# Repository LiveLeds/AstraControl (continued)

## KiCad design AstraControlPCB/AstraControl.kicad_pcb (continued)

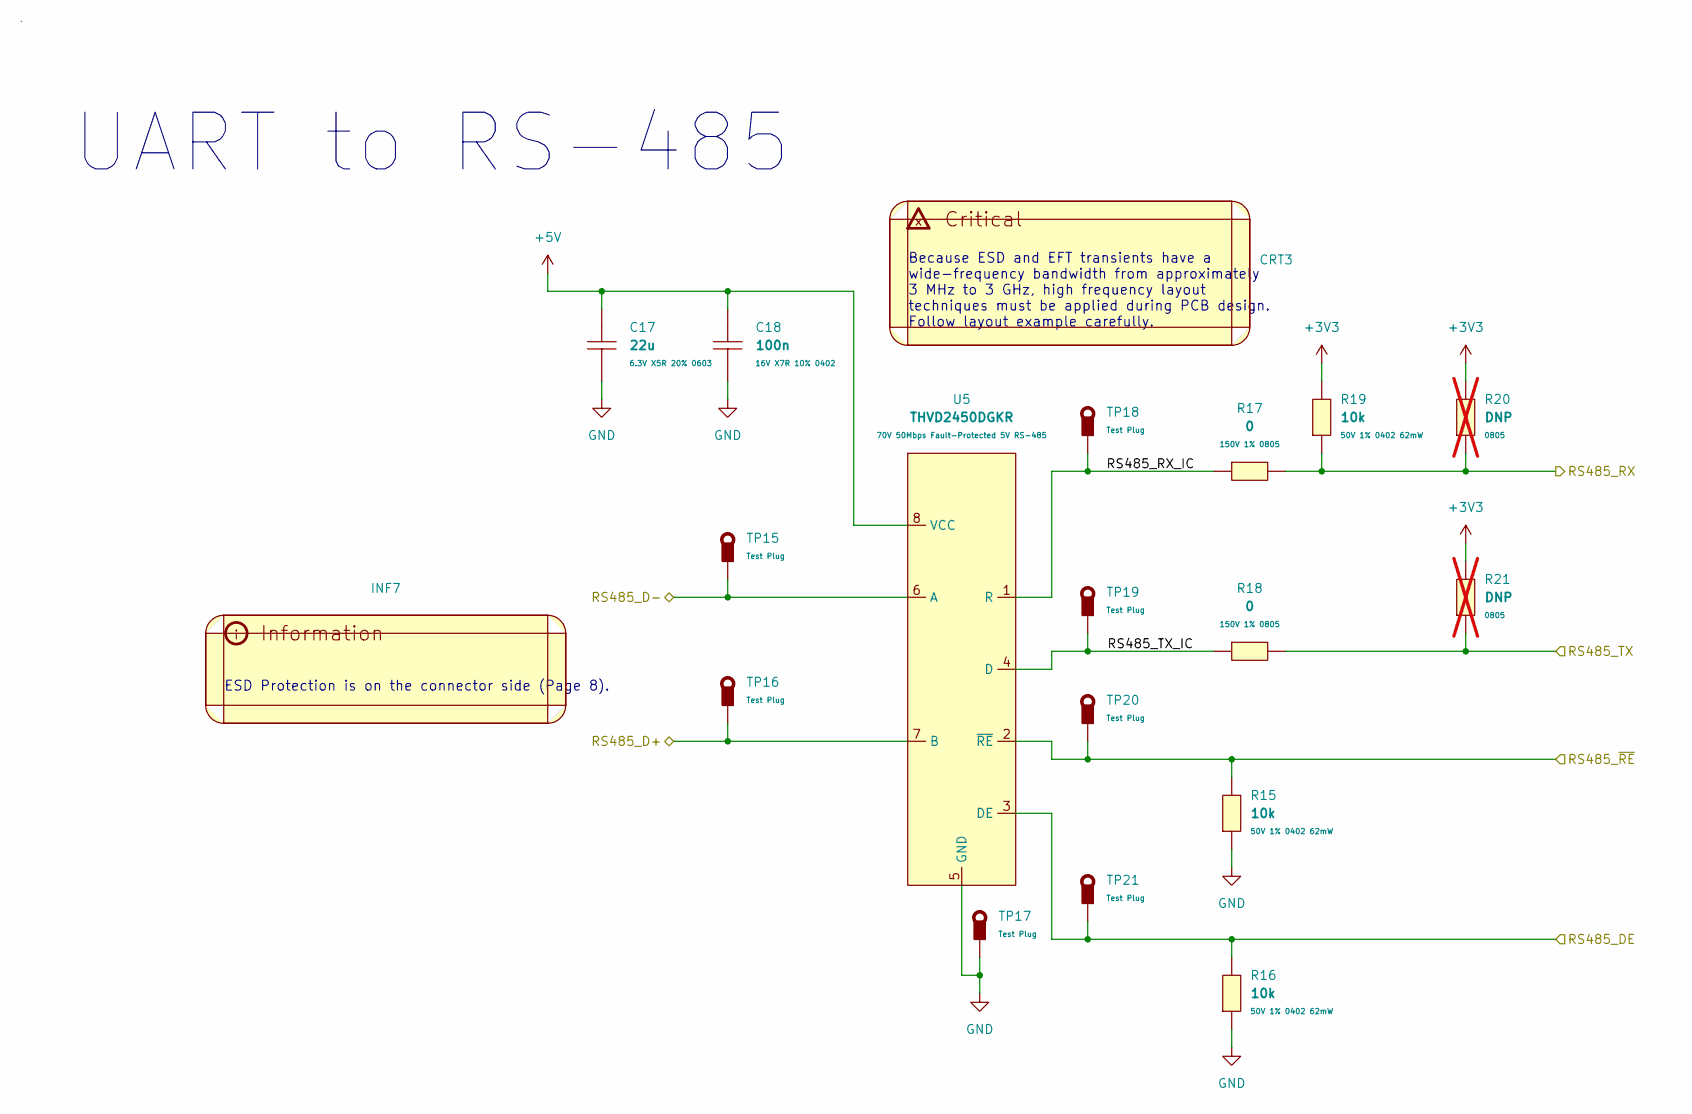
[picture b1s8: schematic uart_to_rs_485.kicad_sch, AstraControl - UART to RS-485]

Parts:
C17: 22u; C_0603_1608Metric; MPN CL10A226MQ8NRNC; LCSC Part C59461
C18: 100n; C_0402_1005Metric; MPN CL05B104KO5NNNC; LCSC Part C1525
CRT3: (no value)
INF7: (no value)
R15, R16, R19: 10k; R_0402_1005Metric; MPN 0402WGF1002TCE; LCSC Part C25744
R17, R18: 0; R_0805_2012Metric_Pad1.20x1.40mm_HandSolder; MPN 0805W8F0000T5E; LCSC Part C17477
R20, R21: DNP; R_DNP_0805_2012Metric_Pad1.20x1.40mm_HandSolder; not fitted
TP15, TP16, TP17, TP18, TP19, TP20, TP21: TestPoint_Thimble; TestPoint_Loop_D3.50mm_Drill0.9mm_Beaded; MPN RH-5000; LCSC Part C5277086
U5: THVD2450DGKR; THVD2450DGKR_RS485_Transciever_VSSOP8; MPN THVD2450DGKR; LCSC Part C3246171

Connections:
+3V3: R19.2, R20.2, R21.2; also elsewhere on the board
+5V: C17.2, C18.2, U5.8 (VCC); also elsewhere on the board
/Block Diagram/MCU/GPIO_4_RS485_TX: R18.2, R21.1; also elsewhere on the board
/Block Diagram/MCU/GPIO_5_RS485_DE: R16.2, TP21.1, U5.3 (DE); also elsewhere on the board
/Block Diagram/MCU/GPIO_6_RS485_RE: R15.2, TP20.1, U5.2 (~RE); also elsewhere on the board
/Block Diagram/MCU/GPIO_7_RS485_RX: R17.2, R19.1, R20.1; also elsewhere on the board
/Block Diagram/Power Connectors/RS485_D+: TP16.1, U5.7 (B); also elsewhere on the board
/Block Diagram/Power Connectors/RS485_D-: TP15.1, U5.6 (A); also elsewhere on the board
/Block Diagram/UART to RS-485/RS485_RX_IC: R17.1, TP18.1, U5.1 (R)
/Block Diagram/UART to RS-485/RS485_TX_IC: R18.1, TP19.1, U5.4 (D)
GND: C17.1, C18.1, R15.1, R16.1, TP17.1, U5.5 (GND); also elsewhere on the board

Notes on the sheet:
Because ESD and EFT transients have a wide-frequency bandwidth from approximately 3 MHz to 3 GHz, high frequency layout techniques must be applied during PCB design. Follow layout example carefully.
UART to RS-485
ESD Protection is on the connector side (Page 8).

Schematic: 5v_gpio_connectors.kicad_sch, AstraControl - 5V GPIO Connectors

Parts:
CN2, CN3: 4P JST VH; JST_VH_B4P-VH-B_1x04_P3.96mm_Vertical; MPN B4P-VH(LF)(SN); LCSC Part C160317

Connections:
+5V_IN: CN2.3, CN3.3; also elsewhere on the board
/Block Diagram/3V3 to 5V Logic Shifter/5V_IO_1: CN2.1; also elsewhere on the board
/Block Diagram/3V3 to 5V Logic Shifter/5V_IO_2: CN2.4; also elsewhere on the board
/Block Diagram/3V3 to 5V Logic Shifter/5V_IO_3: CN3.1; also elsewhere on the board
/Block Diagram/3V3 to 5V Logic Shifter/5V_IO_4: CN3.4; also elsewhere on the board
GND: CN2.2, CN3.2; also elsewhere on the board

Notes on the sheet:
5V GPIO Connectors

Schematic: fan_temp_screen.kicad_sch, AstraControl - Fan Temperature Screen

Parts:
C23: 100p; C_0805_2012Metric_Pad1.18x1.45mm_HandSolder; MPN CL21C101JBANNNC; LCSC Part C1790
CN4, CN5, CN6: 4P JST ZH; JST_ZH_B4B-ZR_1x04_P1.50mm_Vertical; MPN B4B-ZR-3.4(LF)(SN); LCSC Part C163034
INF8: (no value)
R24, R25, R32, R33: 5k1; R_0402_1005Metric; MPN 0402WGF5101TCE; LCSC Part C25905
R26, R29: 0; R_0805_2012Metric_Pad1.20x1.40mm_HandSolder; MPN 0805W8F0000T5E; LCSC Part C17477
R27, R28, R34, R35: DNP; R_DNP_0805_2012Metric_Pad1.20x1.40mm_HandSolder; not fitted
R30: 10k; R_0402_1005Metric; MPN 0402WGF1002TCE; LCSC Part C25744
R31: 3k3; R_0805_2012Metric_Pad1.20x1.40mm_HandSolder; MPN 0805W8F3301T5E; LCSC Part C26010
TP33, TP34, TP35, TP36, TP37, TP38: TestPoint_Thimble; TestPoint_Loop_D3.50mm_Drill0.9mm_Beaded; MPN RH-5000; LCSC Part C5277086

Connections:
+3V3: CN5.2, CN6.2, R24.2, R25.2, R27.2, R28.2, R30.2, R32.2, R33.2, R34.2, R35.2; also elsewhere on the board
+5V_IN: CN4.2; also elsewhere on the board
/Block Diagram/Fan, Temperature and Screen/FAN_PWM: R26.2; also elsewhere on the board
/Block Diagram/Fan, Temperature and Screen/FAN_PWM_CON: CN4.4, R26.1, TP35.1
/Block Diagram/Fan, Temperature and Screen/FAN_TACHO: C23.2, R31.2; also elsewhere on the board
/Block Diagram/Fan, Temperature and Screen/FAN_TACHO_0: R29.2, R30.1, R31.1
/Block Diagram/Fan, Temperature and Screen/FAN_TACHO_CON: CN4.3, R29.1, TP36.1
/Block Diagram/Fan, Temperature and Screen/SCREEN_I2C_SCL: CN6.4, R25.1, R28.1, TP34.1; also elsewhere on the board
/Block Diagram/Fan, Temperature and Screen/SCREEN_I2C_SDA: CN6.3, R33.1, R35.1, TP38.1; also elsewhere on the board
/Block Diagram/Fan, Temperature and Screen/TEMP_I2C_SCL: CN5.4, R24.1, R27.1, TP33.1; also elsewhere on the board
/Block Diagram/Fan, Temperature and Screen/TEMP_I2C_SDA: CN5.3, R32.1, R34.1, TP37.1; also elsewhere on the board
GND: C23.1, CN4.1, CN5.1, CN6.1; also elsewhere on the board

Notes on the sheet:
RC Filter Cutoff: 482KHz
Fan Temperature Screen

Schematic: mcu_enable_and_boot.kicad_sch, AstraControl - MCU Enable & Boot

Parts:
C4: 1u; C_0402_1005Metric; MPN CL05A105KA5NQNC; LCSC Part C52923
C5, C6: 100n; C_0402_1005Metric; MPN CL05B104KO5NNNC; LCSC Part C1525
INF2: (no value)
R3, R5, R6, R7: 0; R_0805_2012Metric_Pad1.20x1.40mm_HandSolder; MPN 0805W8F0000T5E; LCSC Part C17477
R4: 10k; R_0402_1005Metric; MPN 0402WGF1002TCE; LCSC Part C25744
SW1, SW2: TS_Basic_Small; TACTILE_SWITCH-SMD_4P-L5.1-W5.1-P3.70-LS6.5-TL-2; MPN TS-1187A-B-A-B; LCSC Part C318884
TP3, TP4: TestPoint_Thimble; TestPoint_Loop_D3.50mm_Drill0.9mm_Beaded; MPN RH-5000; LCSC Part C5277086

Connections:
+3V3: R3.2; also elsewhere on the board
/Block Diagram/MCU Enable and Boot/BOOT_SW: C5.1, R6.2, SW1.2, TP3.1
/Block Diagram/MCU Enable and Boot/EN_DELAY: C4.1, R4.1, R5.2, R7.2
/Block Diagram/MCU Enable and Boot/EN_DELAY_0: R3.1, R4.2
/Block Diagram/MCU Enable and Boot/EN_SW: C6.2, R5.1, SW2.1, TP4.1
/Block Diagram/MCU Enable and Boot/MCU_BOOT: R6.1; also elsewhere on the board
/Block Diagram/MCU Enable and Boot/MCU_EN: R7.1; also elsewhere on the board
GND: C4.2, C5.2, C6.1, SW1.1, SW2.2; also elsewhere on the board

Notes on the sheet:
MCU Enable & Boot
To ensure that the power supply to the ESP32-S3 chip is stable during power-up, it is advised to add an RC delay circuit at the EN pin.

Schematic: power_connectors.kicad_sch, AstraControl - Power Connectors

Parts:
CN1: 4P JST VH; JST_VH_B4P-VH-B_1x04_P3.96mm_Vertical; MPN B4P-VH(LF)(SN); LCSC Part C160317
D1: NUP3105LT1G; TVS_NUP3105LT1G_36V; MPN BNUP3105LT1G; LCSC Part C2931121
D2: SS14 Schottky; D_SMA_SS14_C2480; MPN SS14; LCSC Part C2480
INF6: (no value)
QST2: (no value)
TP10, TP11: TestPoint_Thimble; TestPoint_Loop_D3.50mm_Drill0.9mm_Beaded; MPN RH-5000; LCSC Part C5277086

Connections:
+5V_IN: CN1.4, D2.1 (K); also elsewhere on the board
/Block Diagram/Power Connectors/RS485_D+: CN1.2, D1.1; also elsewhere on the board
/Block Diagram/Power Connectors/RS485_D-: CN1.3, D1.2; also elsewhere on the board
/Block Diagram/Power Connectors/USB/VBUS: D2.2 (A); also elsewhere on the board
CHASSIS: TP11.1; also elsewhere on the board
GND: CN1.1, D1.3, TP10.1; also elsewhere on the board

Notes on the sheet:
Power connectors
The external power is at 48V, in-case D- or D+ accidentally short to it the TVS diode hopefully doesn't get destroyed immediately. This is the closest diode I found that will not overshoot the clamping voltage of 70V (max tolerated by the tranciever) with V_{BR_MAX} 50V, in stock at JLC and 15pF ca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
Are the TVS diodes enough or should I add anything extra? MOV / TBU?

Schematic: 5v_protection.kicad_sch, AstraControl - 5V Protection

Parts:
C7, C8: 1u; C_0402_1005Metric; MPN CL05A105KA5NQNC; LCSC Part C52923
INF3: (no value)
LED2: LED_RED_20mA_0603; LED_0603_1608Metric; MPN KT-0603R; LCSC Part C2286
R8: 1M; R_0805_2012Metric_Pad1.20x1.40mm_HandSolder; MPN 0805W8F1004T5E; LCSC Part C17514
R9: 220; R_0402_1005Metric; MPN 0402WGF2200TCE; LCSC Part C25091
TP5, TP6: TestPoint_Thimble; TestPoint_Loop_D3.50mm_Drill0.9mm_Beaded; MPN RH-5000; LCSC Part C5277086
U2: NCP361SNT1G; 5V_PROTECTION_NCP361SNT1G_TSOP-5; MPN NCP361SNT1G; LCSC Part C233714

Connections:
+5V: C8.1, LED2.2 (A), U2.5 (OUT); also elsewhere on the board
+5V_IN: C7.2, R8.2, TP5.1, U2.1 (IN); also elsewhere on the board
/Block Diagram/5V Protection/5V_PROT_LED: LED2.1 (K), R9.2
/Block Diagram/5V Protection/FLAG_IC: R8.1, U2.4 (~FLAG)
GND: C7.1, C8.2, R9.1, TP6.1, U2.2 (GND), U2.3 (~EN); also elsewhere on the board

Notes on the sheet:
Over-voltage: 5.67V Under-voltage: 3V Max current: 600mA - 780mA Max V_{IN}: 21V
5V Protection

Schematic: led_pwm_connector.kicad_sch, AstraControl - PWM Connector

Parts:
CN7: JST_VH_8PIN_10A_250V; JST_VH_B8P-VH-B_1x08_P3.96mm_Vertical; MPN B8P-VH-B(LF)(SN); LCSC Part C265117
INF9: (no value)
R36, R37, R38, R39, R40: 0; R_0805_2012Metric_Pad1.20x1.40mm_HandSolder; MPN 0805W8F0000T5E; LCSC Part C17477
TP39, TP40, TP41, TP42, TP43: TestPoint_Thimble; TestPoint_Loop_D3.50mm_Drill0.9mm_Beaded; MPN RH-5000; LCSC Part C5277086

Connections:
+3V3: CN7.7; also elsewhere on the board
+5V_IN: CN7.8; also elsewhere on the board
/Block Diagram/LED PWM Connector/GPIO_15_PWM_CH4: R40.1; also elsewhere on the board
/Block Diagram/LED PWM Connector/GPIO_16_PWM_CH3: R39.1; also elsewhere on the board
/Block Diagram/LED PWM Connector/GPIO_17_PWM_CH2: R38.1; also elsewhere on the board
/Block Diagram/LED PWM Connector/GPIO_18_PWM_CH1: R37.1; also elsewhere on the board
/Block Diagram/LED PWM Connector/PWM_CH1_CONN: CN7.2, R37.2, TP40.1
/Block Diagram/LED PWM Connector/PWM_CH2_CONN: CN7.3, R38.2, TP41.1
/Block Diagram/LED PWM Connector/PWM_CH3_CONN: CN7.4, R39.2, TP42.1
/Block Diagram/LED PWM Connector/PWM_CH4_CONN: CN7.5, R40.2, TP43.1
/Block Diagram/LED PWM Connector/RESERVED_PIN: CN7.1, R36.2, TP39.1
GND: CN7.6, R36.1; also elsewhere on the board

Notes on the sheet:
PWM Connector
If a different signal is required here the 0Ohm + PTH will allow a post assembly fix / experimentation. Otherwise, just GND.

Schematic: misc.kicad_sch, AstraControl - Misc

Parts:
C25, C26, C27, C28: 10n; C_0805_2012Metric_Pad1.18x1.45mm_HandSolder; MPN FV21X103K102ECG; LCSC Part C565682
R45: 1M; R_0805_2012Metric_Pad1.20x1.40mm_HandSolder; MPN 0805W8F1004T5E; LCSC Part C17514
R46, R47, R48: DNP; R_DNP_0805_2012Metric_Pad1.20x1.40mm_HandSolder; not fitted
RING1: AstraControl_Ground_Ring

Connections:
CHASSIS: C25.2, C26.2, C27.2, C28.2, R45.2, R46.2, R47.2, R48.2, RING1.1 (2); also elsewhere on the board
GND: C25.1, C26.1, C27.1, C28.1, R45.1, R46.1, R47.1, R48.1; also elsewhere on the board

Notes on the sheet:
Misc

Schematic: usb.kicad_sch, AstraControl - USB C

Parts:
C16: 100n; C_0402_1005Metric; MPN CL05B104KO5NNNC; LCSC Part C1525
CRT2: (no value)
R13, R14: 5k1; R_0402_1005Metric; MPN 0402WGF5101TCE; LCSC Part C25905
TP12, TP13, TP14: TestPoint_Thimble; TestPoint_Loop_D3.50mm_Drill0.9mm_Beaded; MPN RH-5000; LCSC Part C5277086
U4: USBLC6-2SC6; USBLC6-2SC6_PROTECTION_SOT-23-6; MPN USBLC6-2SC6; LCSC Part C7519
USBC1: TYPE-C-31-M-12; USB_C_Korean_Hroparts_Elec_TYPE-C-31-M-12; MPN TYPE-C-31-M-12; LCSC Part C165948

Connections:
/Block Diagram/MCU/USB_D+: TP14.1, U4.4 (USB_OUT_D+); also elsewhere on the board
/Block Diagram/MCU/USB_D-: TP13.1, U4.6 (USB_OUT_D-); also elsewhere on the board
/Block Diagram/Power Connectors/USB/CC1: R14.2, USBC1.A5 (CC1)
/Block Diagram/Power Connectors/USB/CC2: R13.2, USBC1.B5 (CC2)
/Block Diagram/Power Connectors/USB/USB_CONN_D+: U4.3 (USB_IN_D+), USBC1.A6 (D+), USBC1.B6 (D+)
/Block Diagram/Power Connectors/USB/USB_CONN_D-: U4.1 (USB_IN_D-), USBC1.A7 (D-), USBC1.B7 (D-)
/Block Diagram/Power Connectors/USB/VBUS: C16.2, TP12.1, U4.5 (VBUS), USBC1.A4 (VBUS), USBC1.A9 (VBUS), USBC1.B4 (VBUS), USBC1.B9 (VBUS); also elsewhere on the board
CHASSIS: USBC1.S1 (SHIELD); also elsewhere on the board
GND: C16.1, R13.1, R14.1, U4.2 (GND), USBC1.A1 (GND), USBC1.A12 (GND), USBC1.B1 (GND), USBC1.B12 (GND); also elsewhere on the board

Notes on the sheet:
Route carefully for good performance ESD protection. Place the protection IC as close as possible to the connector.
USB C

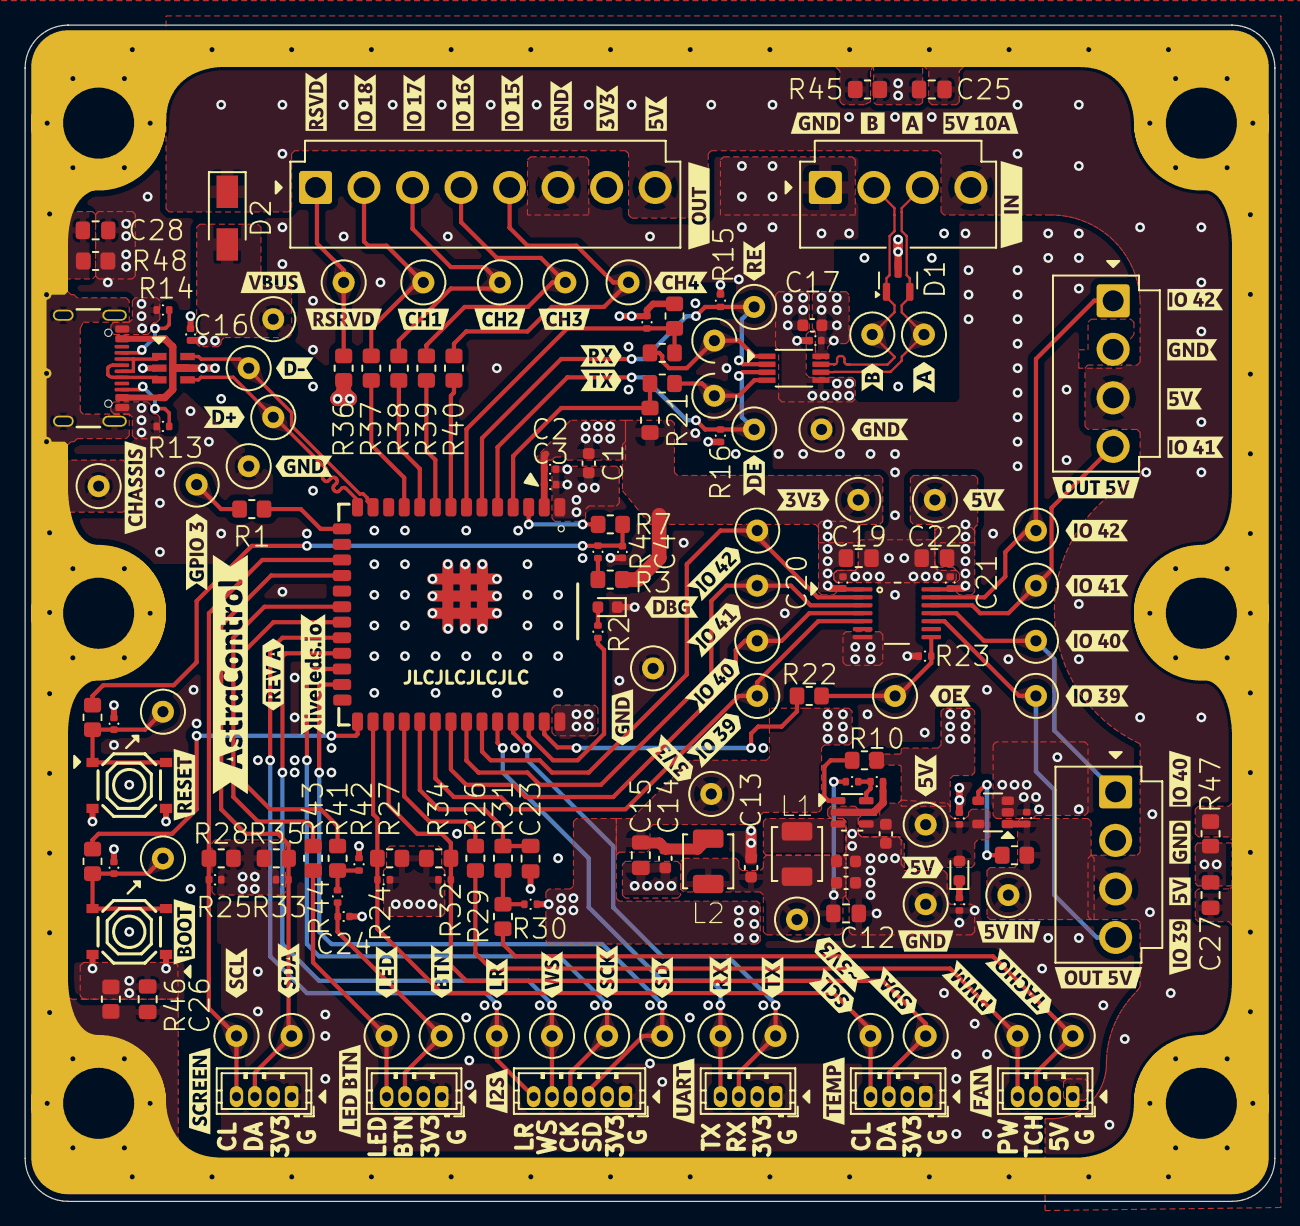
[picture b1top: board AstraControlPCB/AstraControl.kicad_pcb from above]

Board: 4 copper layers, 102.0 x 96.0 mm, 239 parts (0 on the bottom side), 75 nets.

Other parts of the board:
kibuzzard-66F01B73: G***; kibuzzard-66F01B73
kibuzzard-66F01BD1, kibuzzard-66F01BD1#2: G***; kibuzzard-66F01BD1
kibuzzard-66F02A18: G***; kibuzzard-66F02A18
kibuzzard-66F02A25: G***; kibuzzard-66F02A25
kibuzzard-66F02CE1: G***; kibuzzard-66F02CE1
kibuzzard-66F02E3A: G***; kibuzzard-66F02E3A
kibuzzard-66F02E21: G***; kibuzzard-66F02E21
kibuzzard-66F02E40: G***; kibuzzard-66F02E40
kibuzzard-66F05E4B: G***; kibuzzard-66F05E4B
kibuzzard-66F05E43: G***; kibuzzard-66F05E43
kibuzzard-66F024F1: G***; kibuzzard-66F024F1
kibuzzard-66F028F2: G***; kibuzzard-66F028F2
kibuzzard-66F031E5: G***; kibuzzard-66F031E5
kibuzzard-66F032A6: G***; kibuzzard-66F032A6
kibuzzard-66F032D3: G***; kibuzzard-66F032D3
kibuzzard-66F060F2: G***; kibuzzard-66F060F2
kibuzzard-66F060F9: G***; kibuzzard-66F060F9
kibuzzard-66F061A6: G***; kibuzzard-66F061A6
kibuzzard-66F061AE: G***; kibuzzard-66F061AE
kibuzzard-66F061E1: G***; kibuzzard-66F061E1
kibuzzard-66F062BD: G***; kibuzzard-66F062BD
kibuzzard-66F062CA: G***; kibuzzard-66F062CA
kibuzzard-66F065A1: G***; kibuzzard-66F065A1
kibuzzard-66F065A8: G***; kibuzzard-66F065A8
kibuzzard-66F98CDC: G***; kibuzzard-66F98CDC
kibuzzard-66F98D7E: G***; kibuzzard-66F98D7E
kibuzzard-66F98D22: G***; kibuzzard-66F98D22
kibuzzard-66F98D45: G***; kibuzzard-66F98D45
kibuzzard-66F98D78: G***; kibuzzard-66F98D78
kibuzzard-66F98D84: G***; kibuzzard-66F98D84
kibuzzard-66F98D94: G***; kibuzzard-66F98D94
kibuzzard-66F98E12: G***; kibuzzard-66F98E12
kibuzzard-66F0289E: G***; kibuzzard-66F0289E
kibuzzard-66F0312D, kibuzzard-66F0312D#2: G***; kibuzzard-66F0312D
kibuzzard-66F318D2: G***; kibuzzard-66F318D2
kibuzzard-66F318EB: G***; kibuzzard-66F318EB
kibuzzard-66F318FB: G***; kibuzzard-66F318FB
kibuzzard-66F0320C: G***; kibuzzard-66F0320C
kibuzzard-66F0322C: G***; kibuzzard-66F0322C
kibuzzard-66F0328E: G***; kibuzzard-66F0328E
kibuzzard-66F0329C: G***; kibuzzard-66F0329C
kibuzzard-66F0610C: G***; kibuzzard-66F0610C
kibuzzard-66F0624E: G***; kibuzzard-66F0624E
kibuzzard-66F0625D: G***; kibuzzard-66F0625D
kibuzzard-66F0626F: G***; kibuzzard-66F0626F
kibuzzard-66F0631B: G***; kibuzzard-66F0631B
kibuzzard-66F0633C: G***; kibuzzard-66F0633C
kibuzzard-66F0634D: G***; kibuzzard-66F0634D
kibuzzard-66F0646E: G***; kibuzzard-66F0646E
kibuzzard-66F1184E: G***; kibuzzard-66F1184E
kibuzzard-66F1185F: G***; kibuzzard-66F1185F
kibuzzard-66F02423: G***; kibuzzard-66F02423
kibuzzard-66F02606: G***; kibuzzard-66F02606
kibuzzard-66F02656: G***; kibuzzard-66F02656
kibuzzard-66F02873: G***; kibuzzard-66F02873
kibuzzard-66F02898: G***; kibuzzard-66F02898
kibuzzard-66F02927: G***; kibuzzard-66F02927
kibuzzard-66F02986: G***; kibuzzard-66F02986
kibuzzard-66F3192A: G***; kibuzzard-66F3192A
kibuzzard-66F3224A: G***; kibuzzard-66F3224A
kibuzzard-66F03259: G***; kibuzzard-66F03259
kibuzzard-66F03295: G***; kibuzzard-66F03295
kibuzzard-66F06107: G***; kibuzzard-66F06107
kibuzzard-66F06113: G***; kibuzzard-66F06113
kibuzzard-66F06118: G***; kibuzzard-66F06118
kibuzzard-66F06253: G***; kibuzzard-66F06253
kibuzzard-66F06263: G***; kibuzzard-66F06263
kibuzzard-66F06289: G***; kibuzzard-66F06289
kibuzzard-66F06315: G***; kibuzzard-66F06315
kibuzzard-66F06320: G***; kibuzzard-66F06320
kibuzzard-66F06327: G***; kibuzzard-66F06327
kibuzzard-66F06341: G***; kibuzzard-66F06341
kibuzzard-66F06346: G***; kibuzzard-66F06346
kibuzzard-66F06456: G***; kibuzzard-66F06456
kibuzzard-66F31907: G***; kibuzzard-66F31907
kibuzzard-66F31918: G***; kibuzzard-66F31918
kibuzzard-66F32251: G***; kibuzzard-66F32251
kibuzzard-66FAE210: G***; kibuzzard-66FAE210
kibuzzard-66FAE361: G***; kibuzzard-66FAE361
kibuzzard-66FAEE52: G***; kibuzzard-66FAEE52
kibuzzard-674A0EEB: G***; kibuzzard-674A0EEB
kibuzzard-67432C36: G***; kibuzzard-67432C36
kibuzzard-67432CB0: G***; kibuzzard-67432CB0
kibuzzard-67433080: G***; kibuzzard-67433080

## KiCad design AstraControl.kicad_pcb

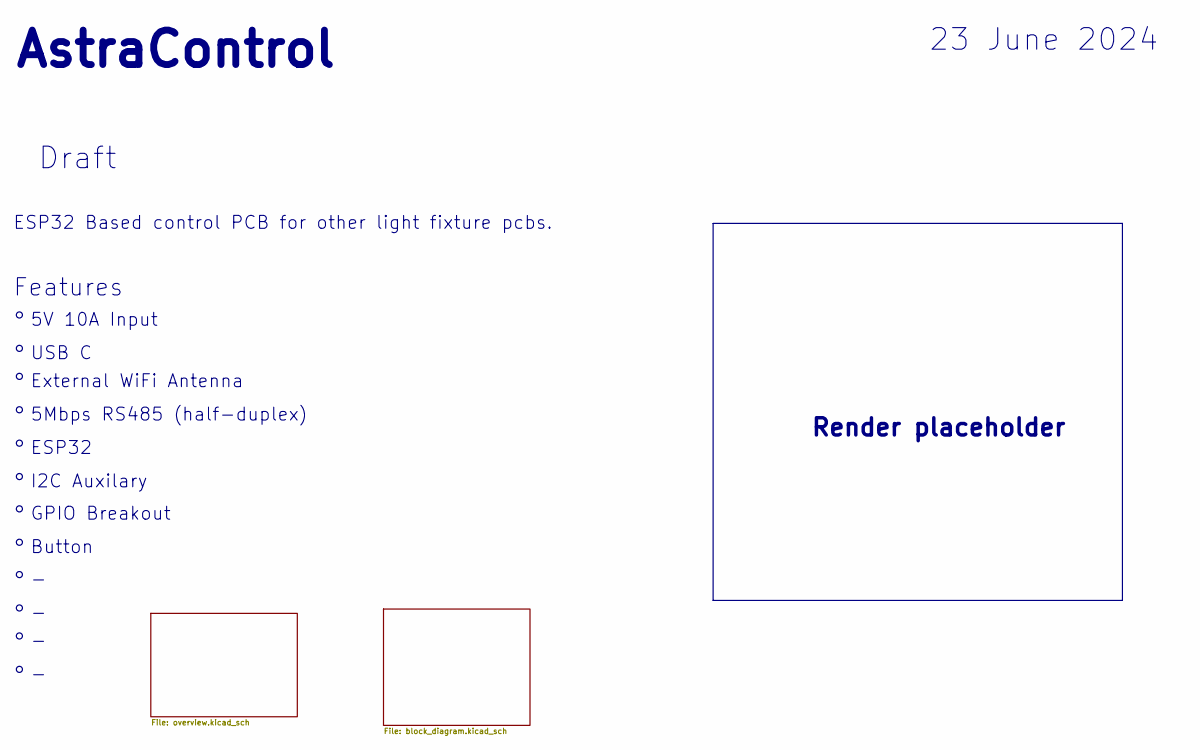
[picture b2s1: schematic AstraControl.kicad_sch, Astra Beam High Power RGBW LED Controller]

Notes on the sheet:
Button
Render placeholder
USB C
I2C Auxilary
23 June 2024
ESP32 Based control PCB for other light fixture pcbs.
AstraControl
External WiFi Antenna
ESP32
Draft
5V 10A Input
GPIO Breakout
Features
5Mbps RS485 (half-duplex)

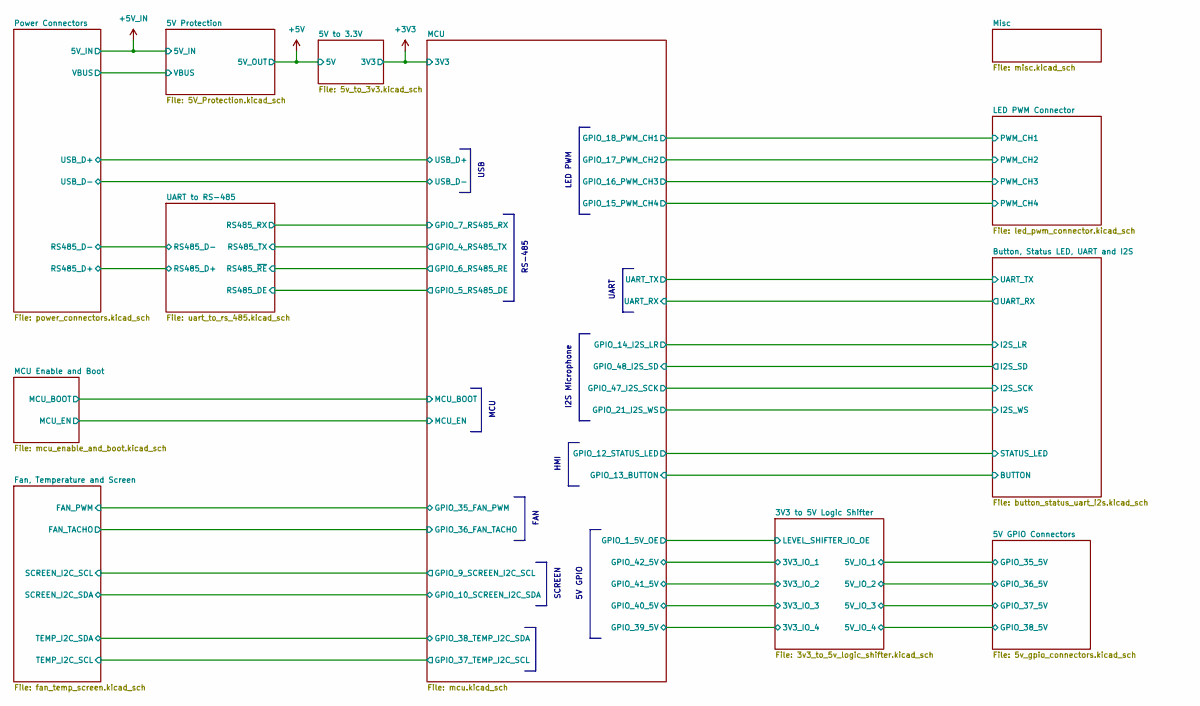
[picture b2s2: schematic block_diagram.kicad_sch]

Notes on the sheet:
USB
FAN
LED PWM
MCU
I2S Microphone
5V GPIO
RS-485
UART
SCREEN
HMI

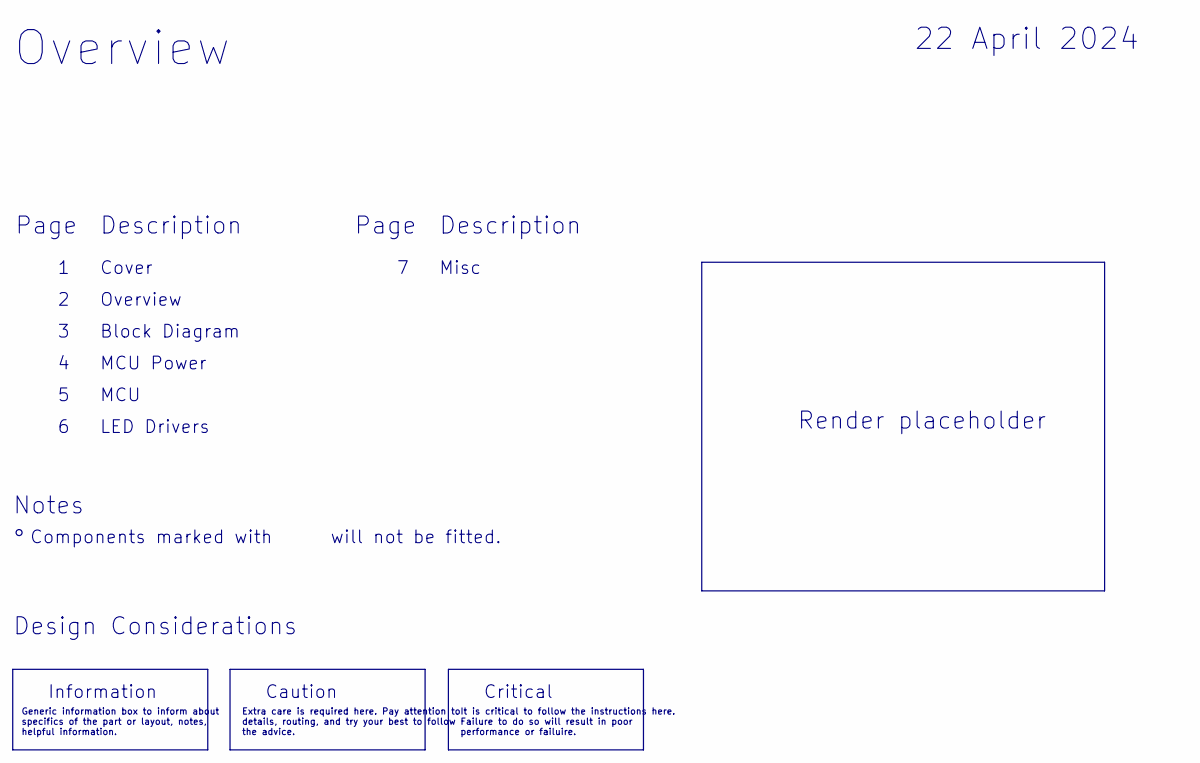
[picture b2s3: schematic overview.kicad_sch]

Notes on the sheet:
Notes
Description
LED Drivers
22 April 2024
MCU
Page
Generic information box to inform about specifics of the part or layout, notes, helpful information.
Extra care is required here. Pay attention to details, routing, and try your best to follow the advice.
It is critical to follow the instructions here. Failure to do so will result in poor performance or failuire.
Overview
Cover
Information
Design Considerations
Components marked with will not be fitted.
Render placeholder
Critical
MCU Power
Misc
Caution
Block Diagram

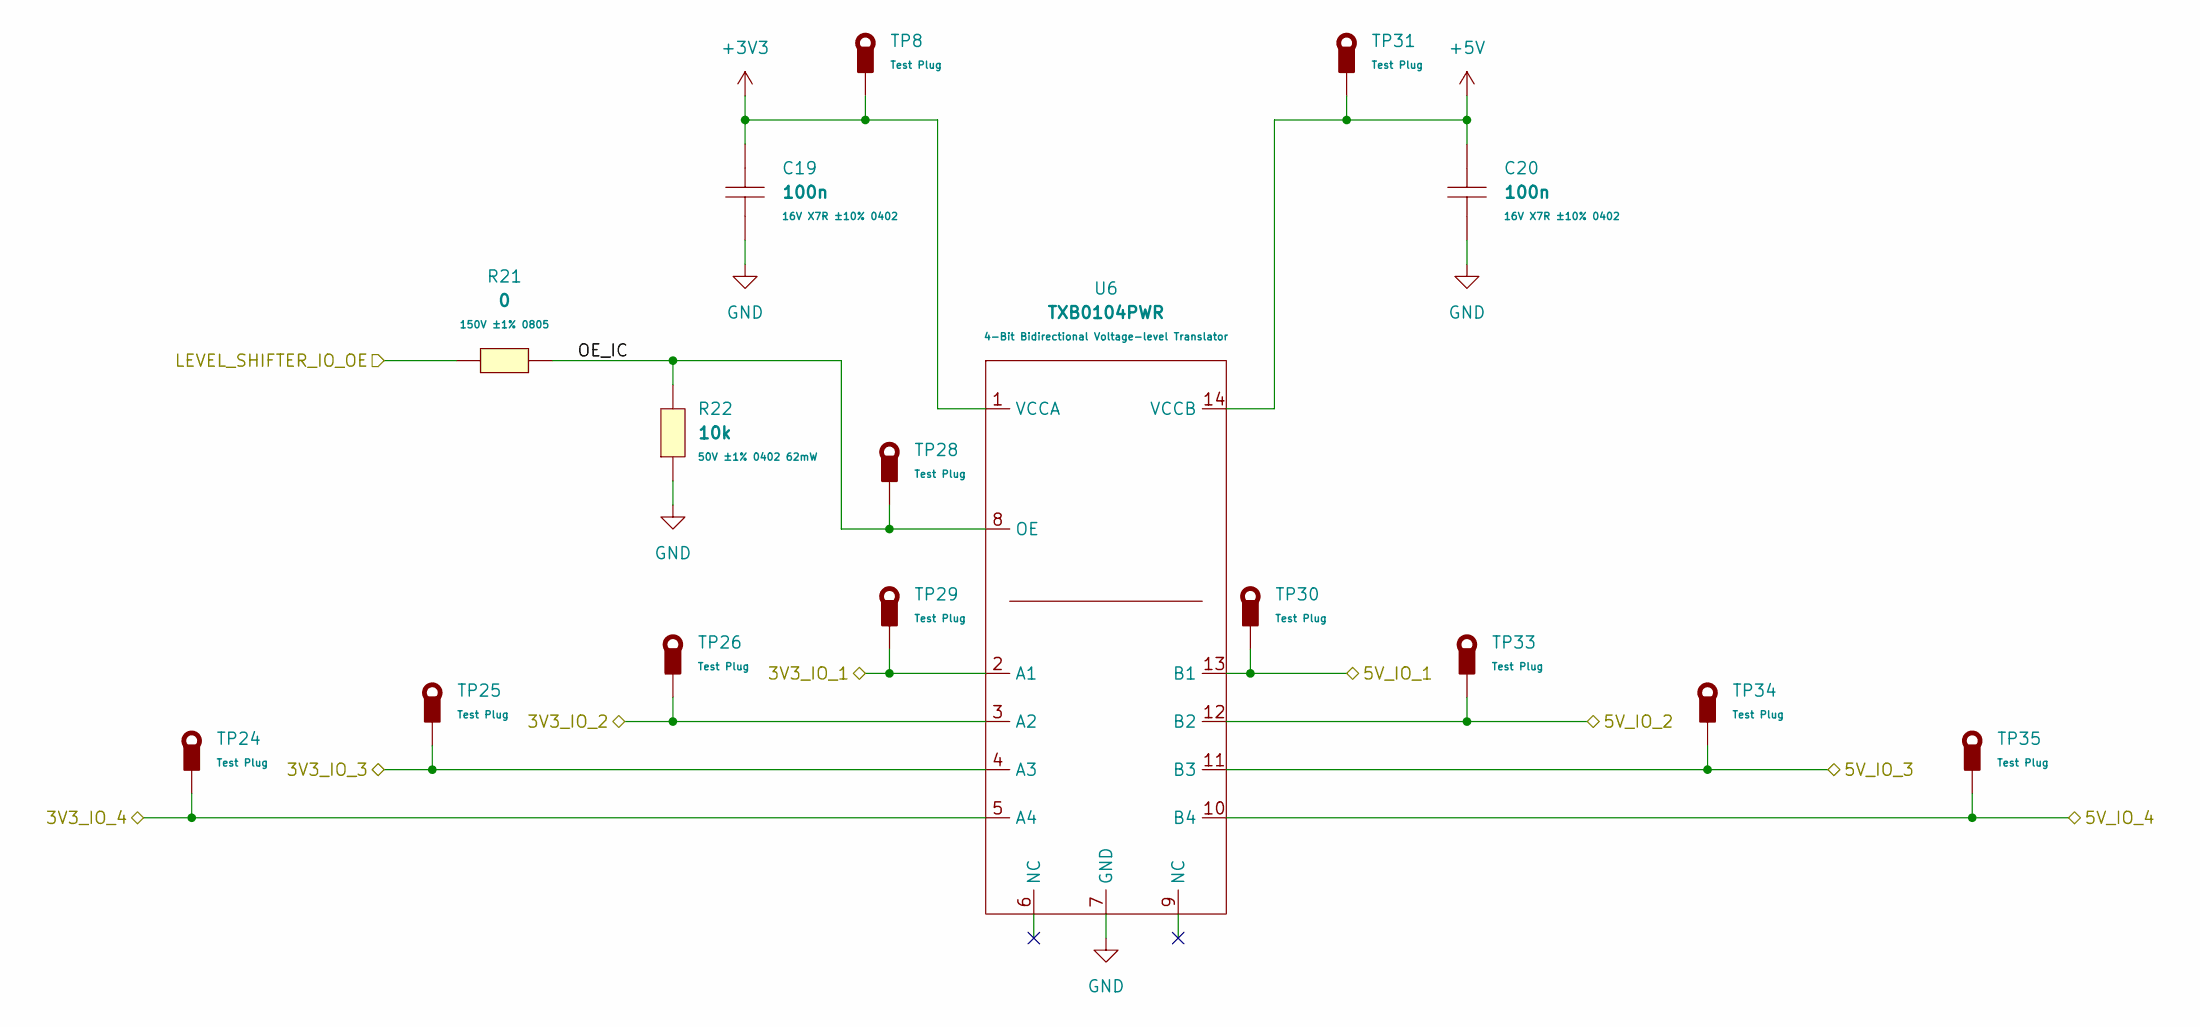
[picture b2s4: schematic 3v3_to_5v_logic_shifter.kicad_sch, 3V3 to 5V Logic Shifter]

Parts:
C19, C20: 100n; C_0402_1005Metric; LCSC Part C1525
R21: 0; R_0805_2012Metric_Pad1.20x1.40mm_HandSolder; LCSC Part C17477
R22: 10k; R_0402_1005Metric; LCSC Part C25744
TP8, TP24, TP25, TP26, TP28, TP29, TP30, TP31, TP33, TP34, TP35: TestPoint_Thimble; TestPoint_Loop_D3.50mm_Drill0.9mm_Beaded; LCSC Part C5277086
U6: TXB0104PWR; LOGIC_SHIFTER_TXB0104PWR_TSOP_14; LCSC Part C60708

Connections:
+3V3: C19.2, TP8.1, U6.1 (VCCA); also elsewhere on the board
+5V: C20.2, TP31.1, U6.14 (VCCB); also elsewhere on the board
/Block Diagram/3V3 to 5V Logic Shifter/3V3_IO_1: TP29.1, U6.2 (A1); also elsewhere on the board
/Block Diagram/3V3 to 5V Logic Shifter/3V3_IO_2: TP26.1, U6.3 (A2); also elsewhere on the board
/Block Diagram/3V3 to 5V Logic Shifter/3V3_IO_3: TP25.1, U6.4 (A3); also elsewhere on the board
/Block Diagram/3V3 to 5V Logic Shifter/3V3_IO_4: TP24.1, U6.5 (A4); also elsewhere on the board
/Block Diagram/3V3 to 5V Logic Shifter/5V_IO_1: TP30.1, U6.13 (B1); also elsewhere on the board
/Block Diagram/3V3 to 5V Logic Shifter/5V_IO_2: TP33.1, U6.12 (B2); also elsewhere on the board
/Block Diagram/3V3 to 5V Logic Shifter/5V_IO_3: TP34.1, U6.11 (B3); also elsewhere on the board
/Block Diagram/3V3 to 5V Logic Shifter/5V_IO_4: TP35.1, U6.10 (B4); also elsewhere on the board
/Block Diagram/3V3 to 5V Logic Shifter/LEVEL_SHIFTER_IO_OE: R21.1; also elsewhere on the board
/Block Diagram/3V3 to 5V Logic Shifter/OE_IC: R21.2, R22.2, TP28.1, U6.8 (OE)
GND: C19.1, C20.1, R22.1, U6.7 (GND); also elsewhere on the board

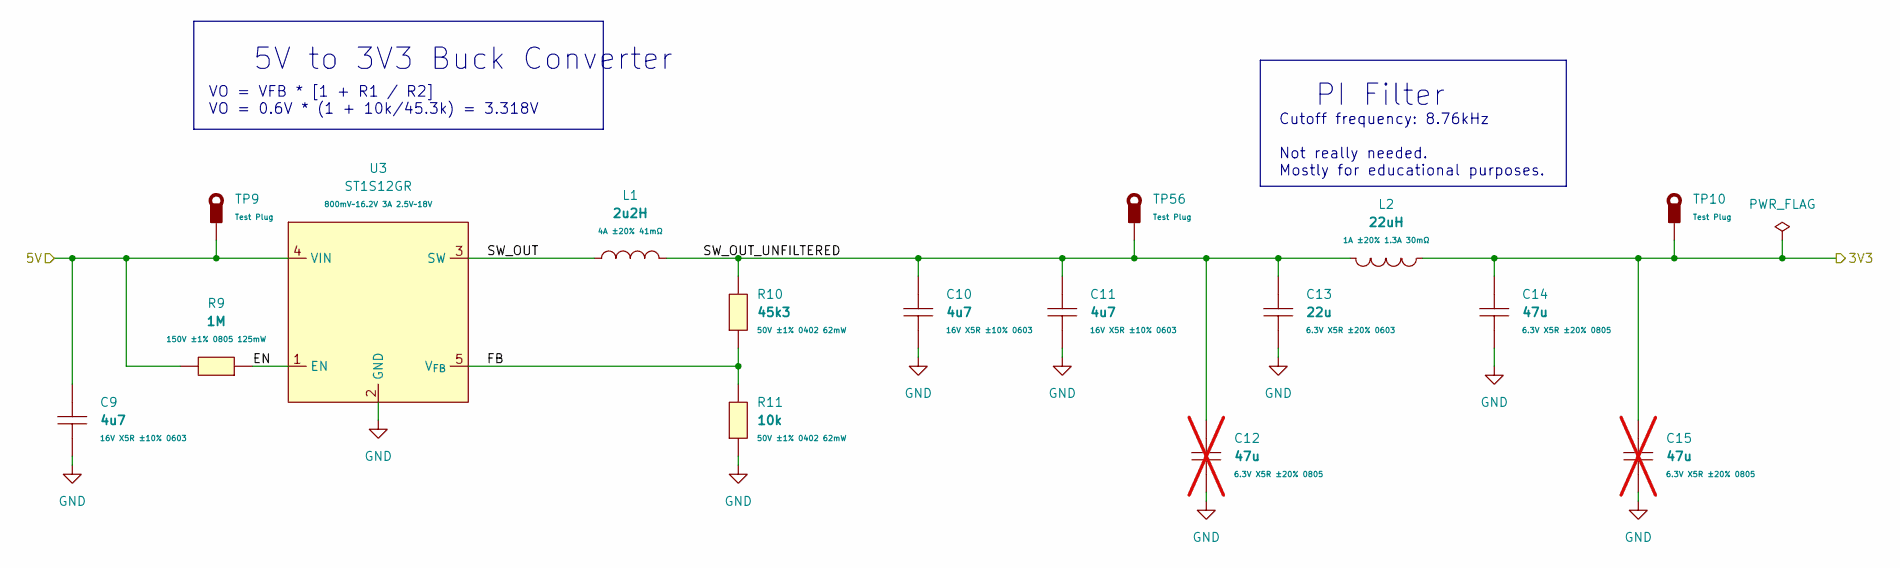
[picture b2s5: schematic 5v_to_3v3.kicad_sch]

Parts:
C9, C10, C11: 4u7; C_0603_1608Metric; LCSC Part C19666
C12, C15: 47u; C_0805_2012Metric_Pad1.18x1.45mm_HandSolder; LCSC Part C16780; not fitted
C13: 22u; C_0603_1608Metric; LCSC Part C59461
C14: 47u; C_0805_2012Metric_Pad1.18x1.45mm_HandSolder; LCSC Part C16780
L1: 2u2H; L_MDA4020_4.1x4.5mm; LCSC Part C2847469
L2: 22uH; L_Sunlord_SWPA4030S; LCSC Part C83472
R9: 1M; R_0805_2012Metric_Pad1.20x1.40mm_HandSolder; LCSC Part C17514
R10: 45k3; R_0402_1005Metric; LCSC Part C26980
R11: 10k; R_0402_1005Metric; LCSC Part C25744
TP9, TP10, TP56: TestPoint_Thimble; TestPoint_Loop_D3.50mm_Drill0.9mm_Beaded; LCSC Part C5277086
U3: ST1S12GR; STEP_DOWN_ST1S12GR_TSOT-23-5; LCSC Part C222072

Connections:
+3V3: C14.2, C15.2, L2.2, TP10.1; also elsewhere on the board
+5V: C9.2, R9.2, TP9.1, U3.4 (VIN); also elsewhere on the board
/Block Diagram/5V to 3.3V/EN: R9.1, U3.1 (EN)
/Block Diagram/5V to 3.3V/FB: R10.1, R11.2, U3.5 (V_{FB})
/Block Diagram/5V to 3.3V/SW_OUT: L1.1, U3.3 (SW)
/Block Diagram/5V to 3.3V/SW_OUT_UNFILTERED: C10.2, C11.2, C12.2, C13.2, L1.2, L2.1, R10.2, TP56.1
GND: C9.1, C10.1, C11.1, C12.1, C13.1, C14.1, C15.1, R11.1, U3.2 (GND); also elsewhere on the board

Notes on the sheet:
5V to 3V3 Buck Converter
VO = VFB * [1 + R1 / R2] VO = 0.6V * (1 + 10k/45.3k) = 3.318V
Cutoff frequency: 8.76kHz Not really needed. Mostly for educational purposes.
PI Filter
